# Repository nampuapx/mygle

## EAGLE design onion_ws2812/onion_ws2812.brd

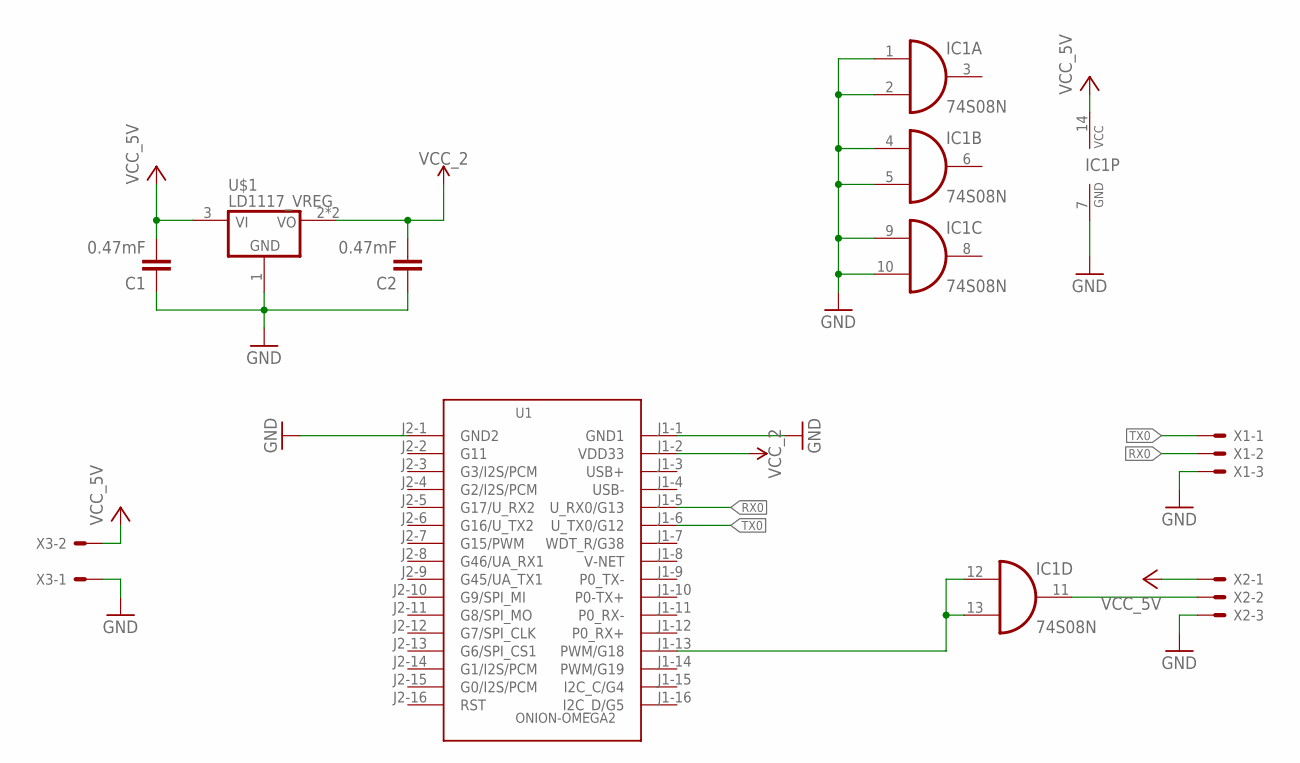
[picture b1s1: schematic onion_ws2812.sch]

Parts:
C1, C2: 0.47mF; C1206
IC1: 74S08N; DIL14
U1: ONION-OMEGA2; ONION-2MM-2X16
U$1: LD1117_VREG; SOT-223
X1, X2: KK-156-3
X3: KK-156-2

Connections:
GND: C1.1, C2.1, IC1.1 (I0), IC1.2 (I1), IC1.4 (I0), IC1.5 (I1), IC1.7 (GND), IC1.9 (I0), IC1.10 (I1), U1.J1-1 (GND1), U1.J2-1 (GND2), U$1.1 (GND), X1.3, X2.3, X3.1
unnamed: IC1.12 (I0), IC1.13 (I1), U1.J1-13 (PWM/G18)
unnamed: IC1.11 (O), X2.2
RX0: U1.J1-5 (U_RX0/G13), X1.2
TX0: U1.J1-6 (U_TX0/G12), X1.1
VCC: C1.2, IC1.14 (VCC), U$1.3 (VIN), X2.1, X3.2
VCC_2: C2.2, U1.J1-2 (VDD33), U$1.2 (VOUT), U$1.TAB (VOUT)

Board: 2 copper layers, 8 parts (0 on the bottom side), 7 nets, no tracks yet.

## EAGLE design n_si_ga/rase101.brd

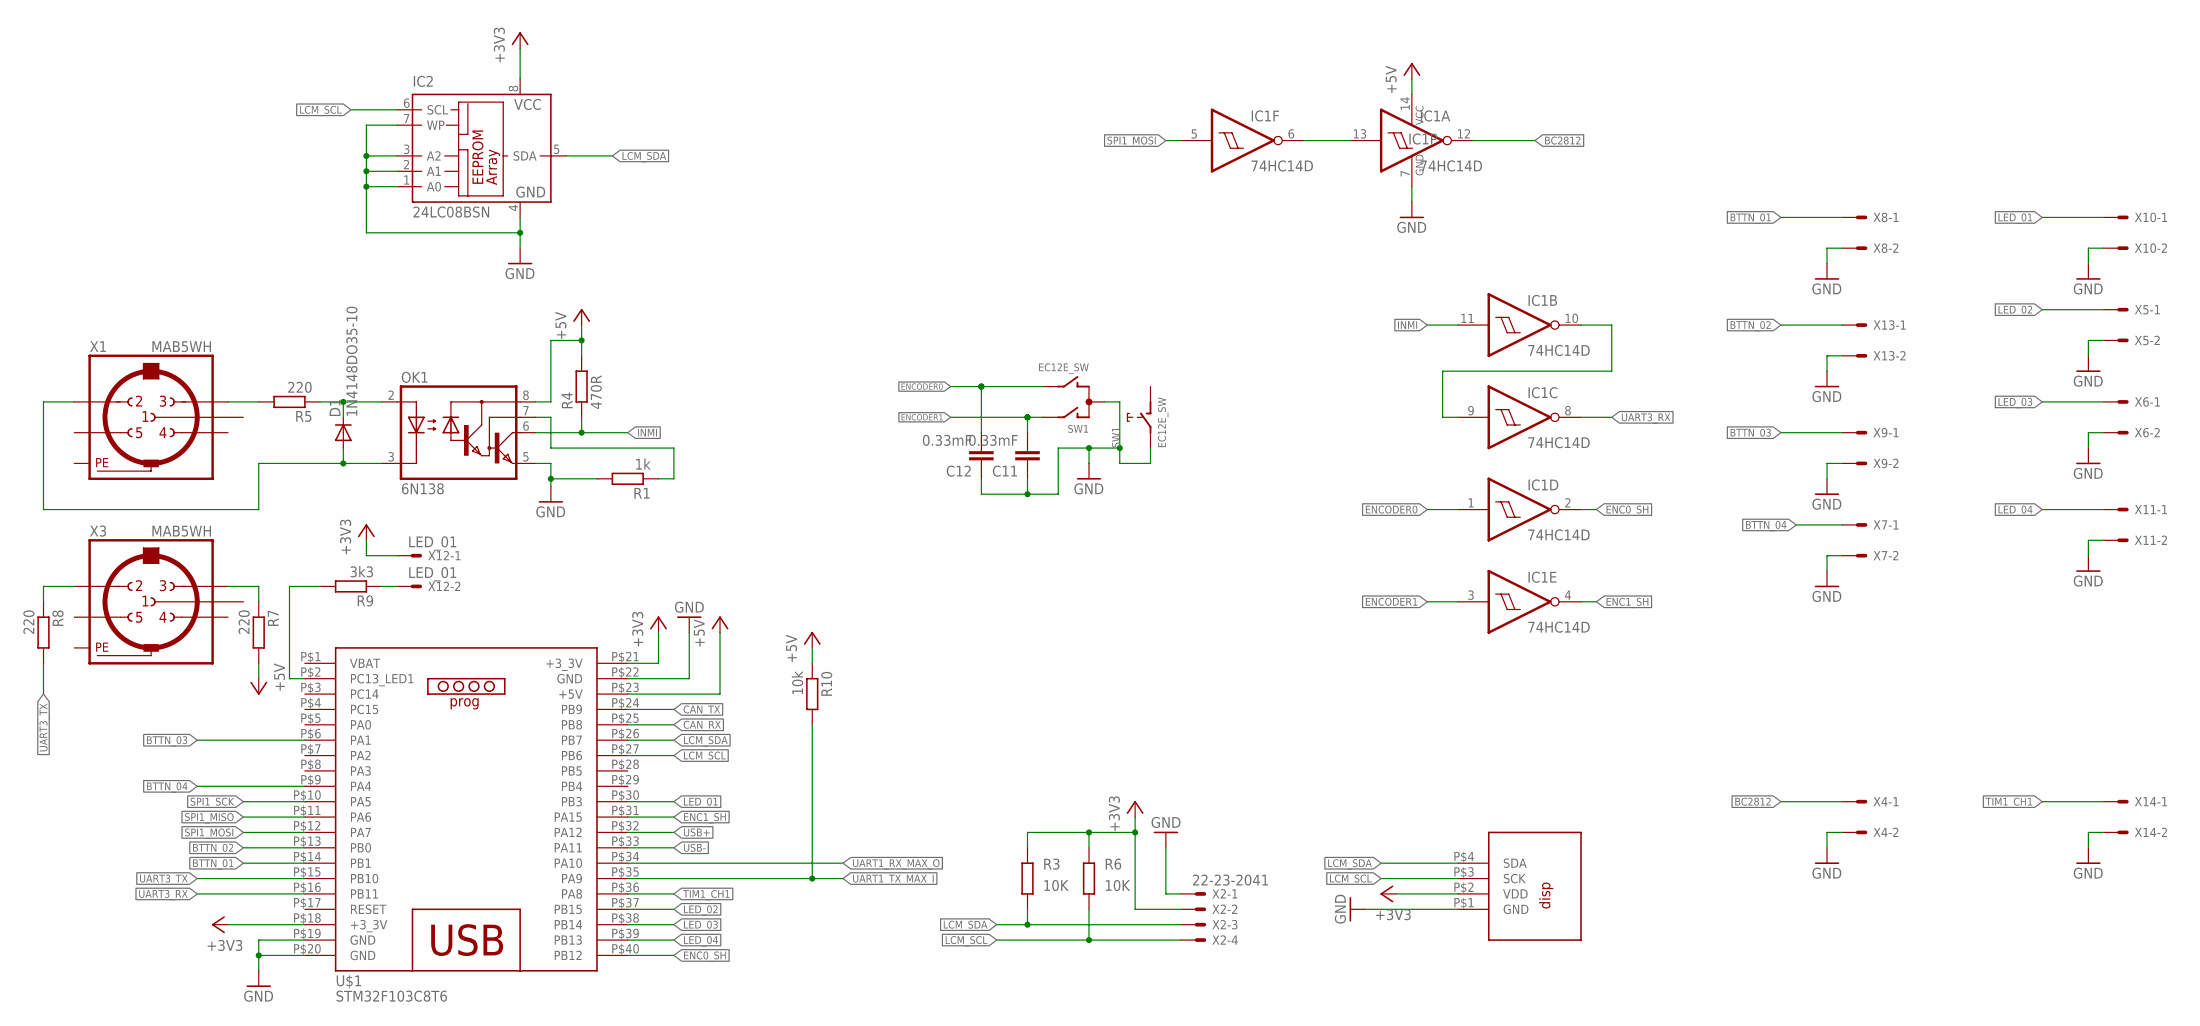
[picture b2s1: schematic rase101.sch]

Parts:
C11, C12: 0.33mF; C1206
D1: 1N4148DO35-10; DO35-10
IC1: 74HC14D; SO14
IC2: 24LC08BSN; SO-08
OK1: 6N138; DIL08
R1: 1k; M1206
R3, R6: 10K; R1206
R4: 470R; M1206
R5, R7, R8: 220; M1206
R9: 3k3; M1206
R10: 10k; M1206
SW1: EC12E_SW; ALPS_EC12E_SW
U$1: STM32F103C8T6
U$3: OLED_0.96
X1, X3: MAB5WH
X2: 22-23-2041
X4, X5, X6, X7, X8, X9, X10, X11, X13, X14: KK-156-2
X12: LED_01; KK-156-2

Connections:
+3V3: IC2.8 (VCC), R3.1, R6.1, U$1.P$18 (+3_3V), U$1.P$21 (+3_3V), U$3.P$2 (VDD), X2.2, X12.1
+5V: IC1.14 (VCC), OK1.8 (VCC), R4.2, R7.2, R10.1, U$1.P$23 (+5V)
BC2812: IC1.12 (O), X4.1
BTTN_01: U$1.P$14 (PB1), X8.1
BTTN_02: U$1.P$13 (PB0), X13.1
BTTN_03: X9.1
BTTN_04: X7.1
CAN_RX: U$1.P$25 (PB8)
CAN_TX: U$1.P$24 (PB9)
ENC0_SH: IC1.2 (O)
ENC1_SH: IC1.4 (O), U$1.P$31 (PA15)
ENCODER0: C12.2, IC1.1 (I), SW1.B
ENCODER1: C11.2, IC1.3 (I), SW1.A
GND: C11.1, C12.1, IC1.7 (GND), IC2.1 (A0), IC2.2 (A1), IC2.3 (A2), IC2.4 (GND), IC2.7 (WP), OK1.5 (GND), R1.2, SW1.C, SW1.E (2), U$1.P$19 (GND), U$1.P$20 (GND), U$1.P$22 (GND), U$3.P$1 (GND), X2.1, X4.2, X5.2, X6.2, X7.2, X8.2, X9.2, X10.2, X11.2, X13.2, X14.2
INMI: IC1.11 (I), OK1.6 (VO), R4.1
LCM_SCL: R6.2, U$1.P$27 (PB6), U$3.P$3 (SCK), X2.4
LCM_SDA: R3.2, U$1.P$26 (PB7), U$3.P$4 (SDA), X2.3
LED_01: U$1.P$30 (PB3), X10.1
LED_02: U$1.P$37 (PB15), X5.1
LED_03: U$1.P$38 (PB14), X6.1
LED_04: U$1.P$39 (PB13), X11.1
unnamed: R8.1, X3.2
unnamed: R7.1, X3.3
unnamed: IC1.9 (I), IC1.10 (O)
unnamed: D1.C, OK1.2 (A), R5.1
unnamed: R5.2, X1.3
unnamed: D1.A, OK1.3 (C), X1.2
unnamed: OK1.7 (VB), R1.1
unnamed: R9.1, X12.2
unnamed: IC1.6 (O), IC1.13 (I)
unnamed: R9.2, U$1.P$2 (PC13_LED1)
PE: X1.PE, X1.PE@ (PE), X3.PE, X3.PE@ (PE)
SPI1_MISO: U$1.P$11 (PA6)
SPI1_MOSI: IC1.5 (I), U$1.P$12 (PA7)
SPI1_SCK: U$1.P$10 (PA5)
TIM1_CH1: U$1.P$36 (PA8), X14.1
UART1_RX_MAX_O: U$1.P$34 (PA10)
UART1_TX_MAX_I: R10.2, U$1.P$35 (PA9)
UART3_RX: IC1.8 (O)
UART3_TX: R8.2
USB+: U$1.P$32 (PA12)
USB-: U$1.P$33 (PA11)

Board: 2 copper layers, 32 parts (6 on the bottom side), 30 nets, no tracks yet.

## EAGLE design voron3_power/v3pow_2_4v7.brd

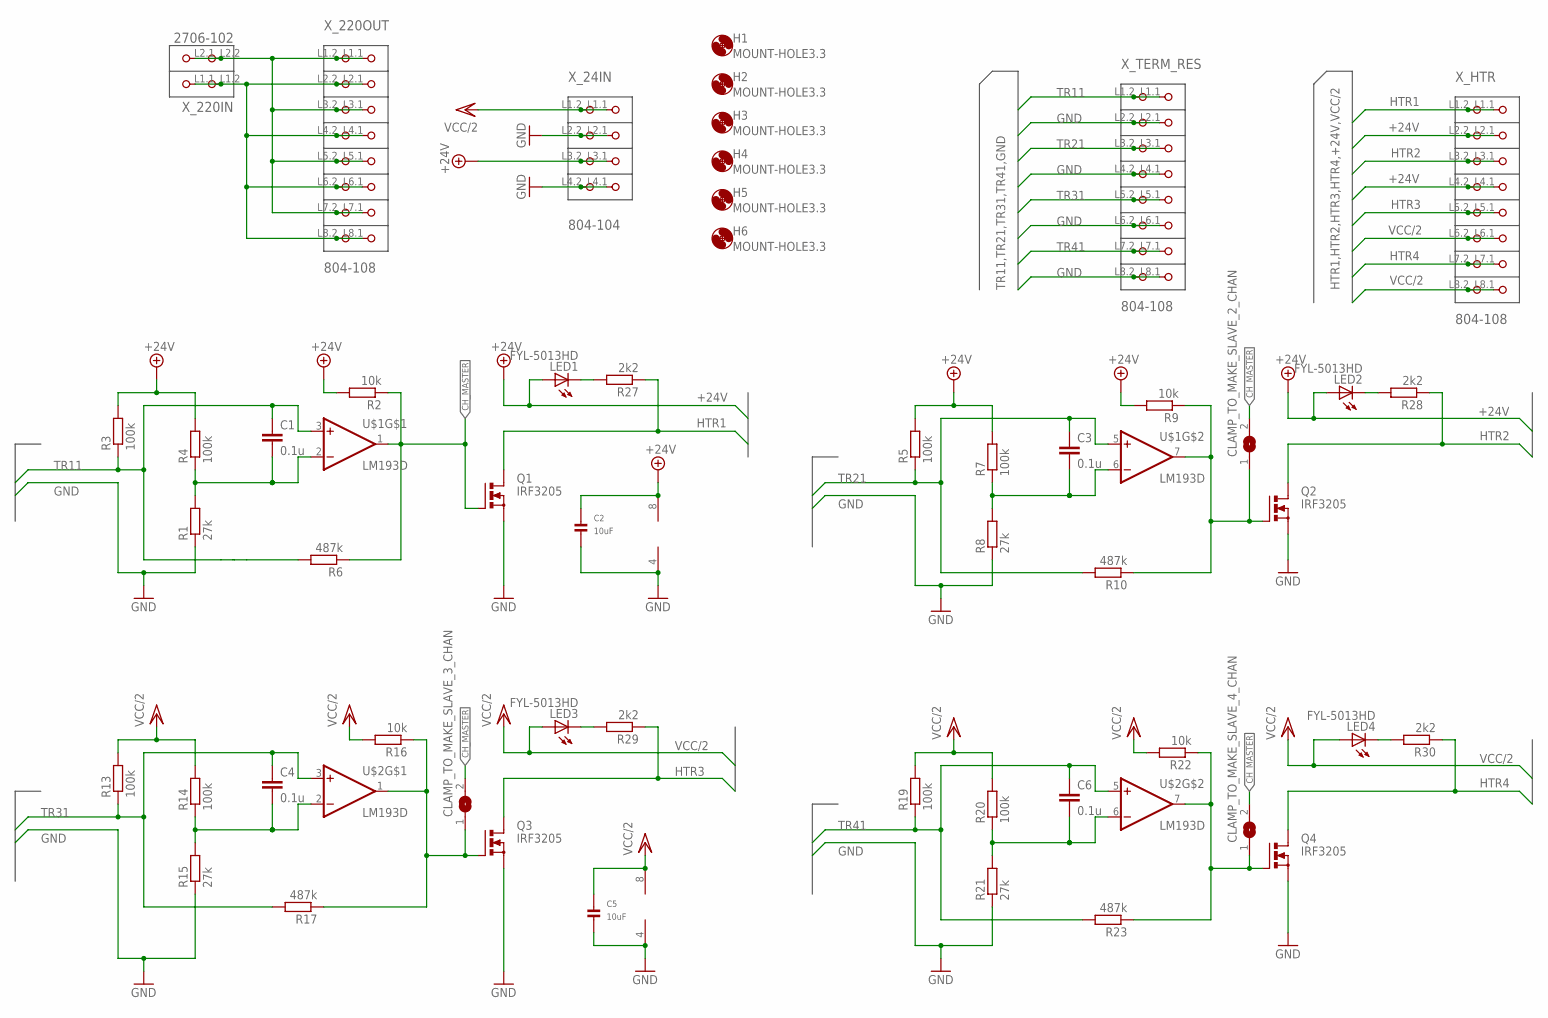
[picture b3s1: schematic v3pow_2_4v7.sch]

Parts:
C1, C3, C4, C6: 0.1u; C0805
C2, C5: 10uF; 1206
CLAMP_TO_MAKE_SLAVE_2_CHAN, CLAMP_TO_MAKE_SLAVE_3_CHAN, CLAMP_TO_MAKE_SLAVE_4_CHAN: SJ
H1, H2, H3, H4, H5, H6: MOUNT-HOLE3.3; 3,3
LED1, LED2, LED3, LED4: FYL-5013HD; LED5MM
Q1, Q2, Q3, Q4: IRF3205; TO220BV
R1, R8, R15, R21: 27k; M0805
R2, R9, R16, R22: 10k; M0805
R3, R4, R5, R7, R13, R14, R19, R20: 100k; M0805
R6, R10, R17, R23: 487k; M0805
R27, R28, R29, R30: 2k2; M0805
U$1, U$2: LM193D; SO08
X_24IN: 804-104; P-804-104
X_220IN: 2706-102; P-2706-102
X_220OUT: 804-108; P-804-108
X_HTR: 804-108; P-804-108
X_TERM_RES: 804-108; P-804-108

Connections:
+24V: C2.1, LED1.A, LED2.A, R2.2, R3.2, R4.2, R5.2, R7.2, R9.2, U$1.8 (V+), X_24IN.L3.1 (P3.1), X_24IN.L3.2 (P3.2), X_HTR.L2.1 (P2.1), X_HTR.L2.2 (P2.2), X_HTR.L4.1 (P4.1), X_HTR.L4.2 (P4.2)
CH_MASTER: CLAMP_TO_MAKE_SLAVE_2_CHAN.2, CLAMP_TO_MAKE_SLAVE_3_CHAN.2, CLAMP_TO_MAKE_SLAVE_4_CHAN.2, Q1.G, R2.1, R6.1, U$1.1 (OUT)
GND: C2.2, C5.2, Q1.S, Q2.S, Q3.S, Q4.S, R1.1, R8.1, R15.1, R21.1, U$1.4 (V-), U$2.4 (V-), X_24IN.L2.1 (P2.1), X_24IN.L2.2 (P2.2), X_24IN.L4.1 (P4.1), X_24IN.L4.2 (P4.2), X_TERM_RES.L2.1 (P2.1), X_TERM_RES.L2.2 (P2.2), X_TERM_RES.L4.1 (P4.1), X_TERM_RES.L4.2 (P4.2), X_TERM_RES.L6.1 (P6.1), X_TERM_RES.L6.2 (P6.2), X_TERM_RES.L8.1 (P8.1), X_TERM_RES.L8.2 (P8.2)
HTR1: Q1.D, R27.1, X_HTR.L1.1 (P1.1), X_HTR.L1.2 (P1.2)
HTR2: Q2.D, R28.1, X_HTR.L3.1 (P3.1), X_HTR.L3.2 (P3.2)
HTR3: Q3.D, R29.1, X_HTR.L5.1 (P5.1), X_HTR.L5.2 (P5.2)
HTR4: Q4.D, R30.1, X_HTR.L7.1 (P7.1), X_HTR.L7.2 (P7.2)
N44: X_220IN.L2.1 (P2.1), X_220IN.L2.2 (P2.2), X_220OUT.L1.1 (P1.1), X_220OUT.L1.2 (P1.2), X_220OUT.L3.1 (P3.1), X_220OUT.L3.2 (P3.2), X_220OUT.L5.1 (P5.1), X_220OUT.L5.2 (P5.2), X_220OUT.L7.1 (P7.1), X_220OUT.L7.2 (P7.2)
unnamed: CLAMP_TO_MAKE_SLAVE_3_CHAN.1, Q3.G, R16.1, R17.1, U$2.1 (OUT)
unnamed: CLAMP_TO_MAKE_SLAVE_2_CHAN.1, Q2.G, R9.1, R10.1, U$1.7 (OUT)
unnamed: CLAMP_TO_MAKE_SLAVE_4_CHAN.1, Q4.G, R22.1, R23.1, U$2.7 (OUT)
unnamed: C3.2, R7.1, R8.2, U$1.6 (-IN)
unnamed: C1.2, R1.2, R4.1, U$1.2 (-IN)
unnamed: C4.2, R14.1, R15.2, U$2.2 (-IN)
unnamed: C6.2, R20.1, R21.2, U$2.6 (-IN)
unnamed: LED1.K (C), R27.2
unnamed: LED2.K (C), R28.2
unnamed: LED3.K (C), R29.2
unnamed: LED4.K (C), R30.2
NN55: X_220IN.L1.1 (P1.1), X_220IN.L1.2 (P1.2), X_220OUT.L2.1 (P2.1), X_220OUT.L2.2 (P2.2), X_220OUT.L4.1 (P4.1), X_220OUT.L4.2 (P4.2), X_220OUT.L6.1 (P6.1), X_220OUT.L6.2 (P6.2), X_220OUT.L8.1 (P8.1), X_220OUT.L8.2 (P8.2)
TR11: C1.1, R3.1, R6.2, U$1.3 (+IN), X_TERM_RES.L1.1 (P1.1), X_TERM_RES.L1.2 (P1.2)
TR21: C3.1, R5.1, R10.2, U$1.5 (+IN), X_TERM_RES.L3.1 (P3.1), X_TERM_RES.L3.2 (P3.2)
TR31: C4.1, R13.1, R17.2, U$2.3 (+IN), X_TERM_RES.L5.1 (P5.1), X_TERM_RES.L5.2 (P5.2)
TR41: C6.1, R19.1, R23.2, U$2.5 (+IN), X_TERM_RES.L7.1 (P7.1), X_TERM_RES.L7.2 (P7.2)
VCC/2: C5.1, LED3.A, LED4.A, R13.2, R14.2, R16.2, R19.2, R20.2, R22.2, U$2.8 (V+), X_24IN.L1.1 (P1.1), X_24IN.L1.2 (P1.2), X_HTR.L6.1 (P6.1), X_HTR.L6.2 (P6.2), X_HTR.L8.1 (P8.1), X_HTR.L8.2 (P8.2)

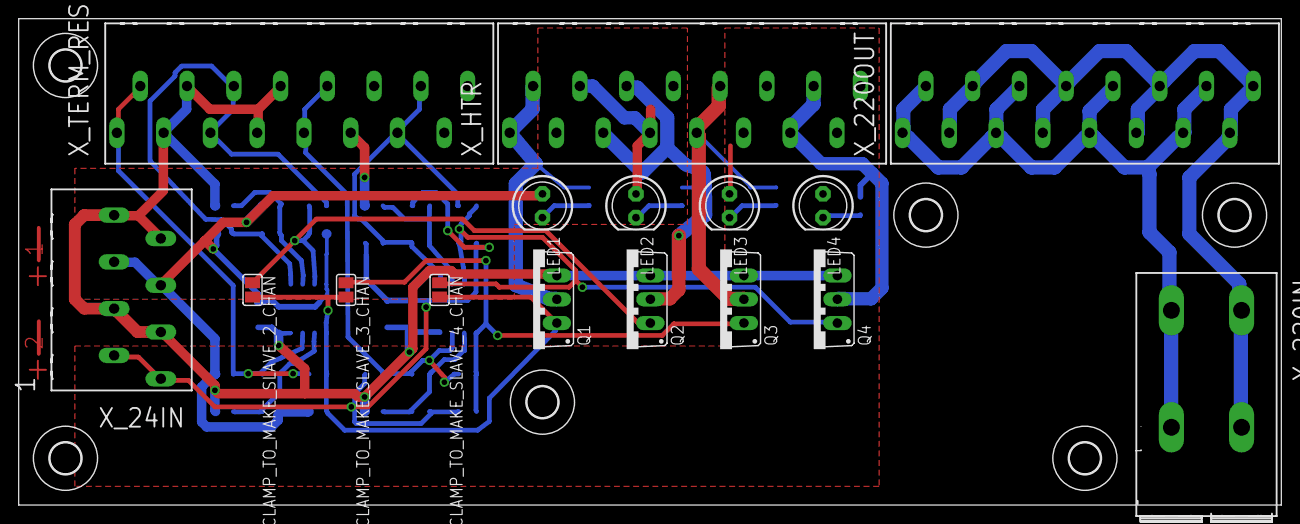
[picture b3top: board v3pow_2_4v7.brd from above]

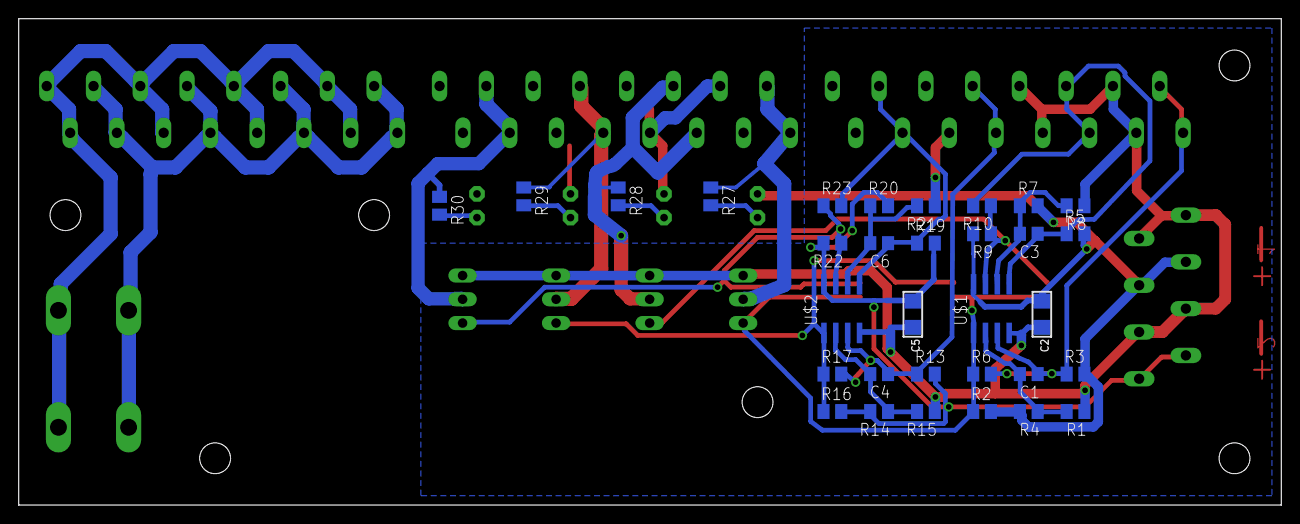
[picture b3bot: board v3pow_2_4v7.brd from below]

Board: 2 copper layers, 135.0 x 52.0 mm, 54 parts (32 on the bottom side), 25 nets.

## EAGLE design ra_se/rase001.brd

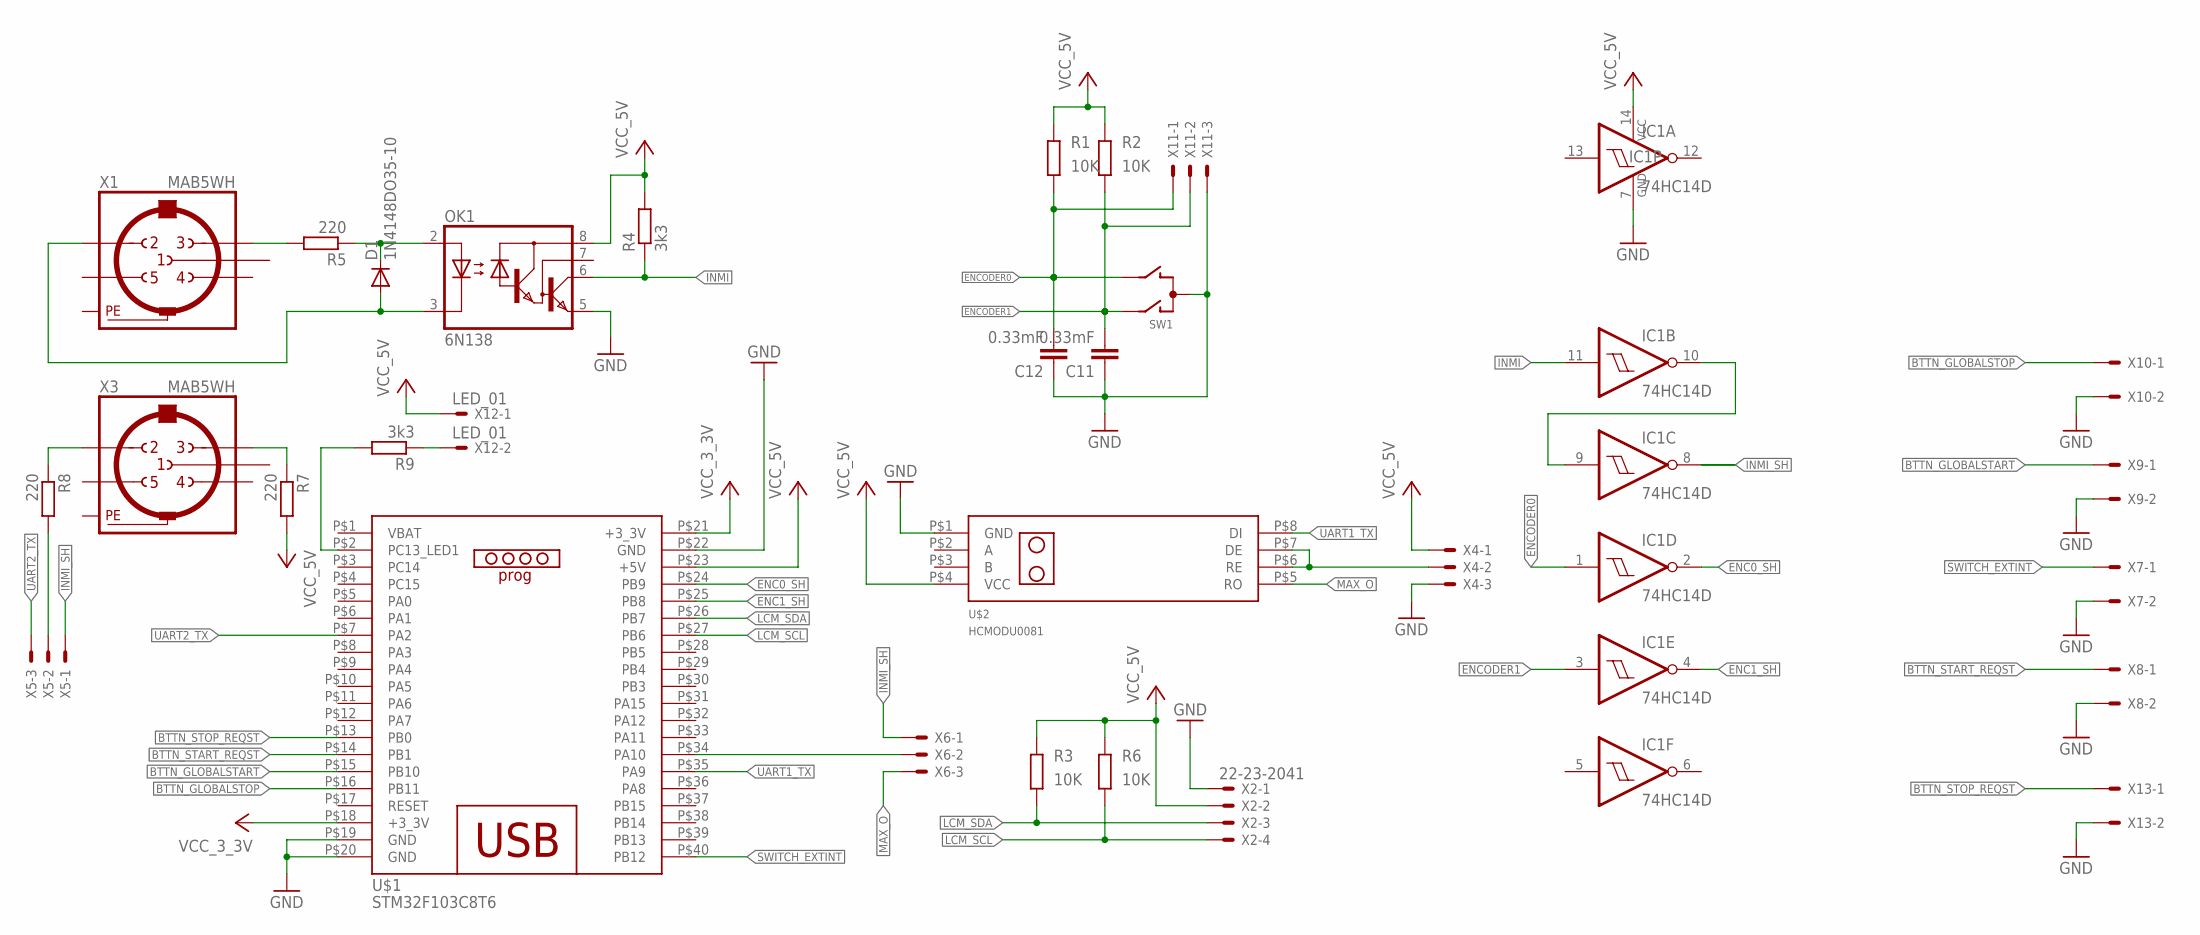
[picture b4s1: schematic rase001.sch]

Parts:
C11, C12: 0.33mF; C1206
D1: 1N4148DO35-10; DO35-10
IC1: 74HC14D; SO14
OK1: 6N138; DIL08
R1, R2, R3, R6: 10K; R1206
R4, R9: 3k3; M1206
R5, R7, R8: 220; M1206
SW1: EC12E_SW; ALPS_EC12E_SW
U$1: STM32F103C8T6
U$2: HCMODU0081
X1, X3: MAB5WH
X2: 22-23-2041
X4, X5, X6, X11: KK-156-3
X7, X8, X9, X10, X13: KK-156-2
X12: LED_01; KK-156-2

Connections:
BTTN_GLOBALSTART: U$1.P$15 (PB10), X9.1
BTTN_GLOBALSTOP: U$1.P$16 (PB11), X10.1
BTTN_START_REQST: U$1.P$14 (PB1), X8.1
BTTN_STOP_REQST: U$1.P$13 (PB0), X13.1
ENC0_SH: IC1.2 (O), U$1.P$24 (PB9)
ENC1_SH: IC1.4 (O), U$1.P$25 (PB8)
ENCODER0: C12.2, R1.2, SW1.B, X11.1
ENCODER1: C11.2, R2.2, SW1.A, X11.2
GND: C11.1, C12.1, IC1.7 (GND), OK1.5 (GND), SW1.C, U$1.P$19 (GND), U$1.P$20 (GND), U$1.P$22 (GND), U$2.P$1 (GND), X2.1, X4.3, X7.2, X8.2, X9.2, X10.2, X11.3, X13.2
INMI: OK1.6 (VO), R4.1
INMI_SH: IC1.8 (O), X5.1, X6.1
LCM_SCL: R6.2, U$1.P$27 (PB6), X2.4
LCM_SDA: R3.2, U$1.P$26 (PB7), X2.3
MAX_O: U$2.P$5 (RO), X6.3
unnamed: R8.1, X3.2
unnamed: R7.1, X3.3
unnamed: IC1.9 (I), IC1.10 (O)
unnamed: D1.C, OK1.2 (A), R5.1
unnamed: R5.2, X1.3
unnamed: D1.A, OK1.3 (C), X1.2
unnamed: R8.2, X5.2
unnamed: R9.1, X12.2
unnamed: U$1.P$34 (PA10), X6.2
unnamed: U$2.P$6 (RE), U$2.P$7 (DE), X4.2
unnamed: R9.2, U$1.P$2 (PC13_LED1)
PE: X1.PE, X1.PE@ (PE), X3.PE, X3.PE@ (PE)
SWITCH_EXTINT: U$1.P$40 (PB12), X7.1
UART1_TX: U$1.P$35 (PA9), U$2.P$8 (DI)
UART2_TX: U$1.P$7 (PA2), X5.3
VCC: IC1.14 (VCC)
VCC_3V: U$1.P$18 (+3_3V), U$1.P$21 (+3_3V)
VCC_5V: OK1.8 (VCC), R1.1, R2.1, R3.1, R4.2, R6.1, R7.2, U$1.P$23 (+5V), U$2.P$4 (VCC), X2.2, X4.1, X12.1

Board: 2 copper layers, 30 parts (0 on the bottom side), 31 nets, no tracks yet.

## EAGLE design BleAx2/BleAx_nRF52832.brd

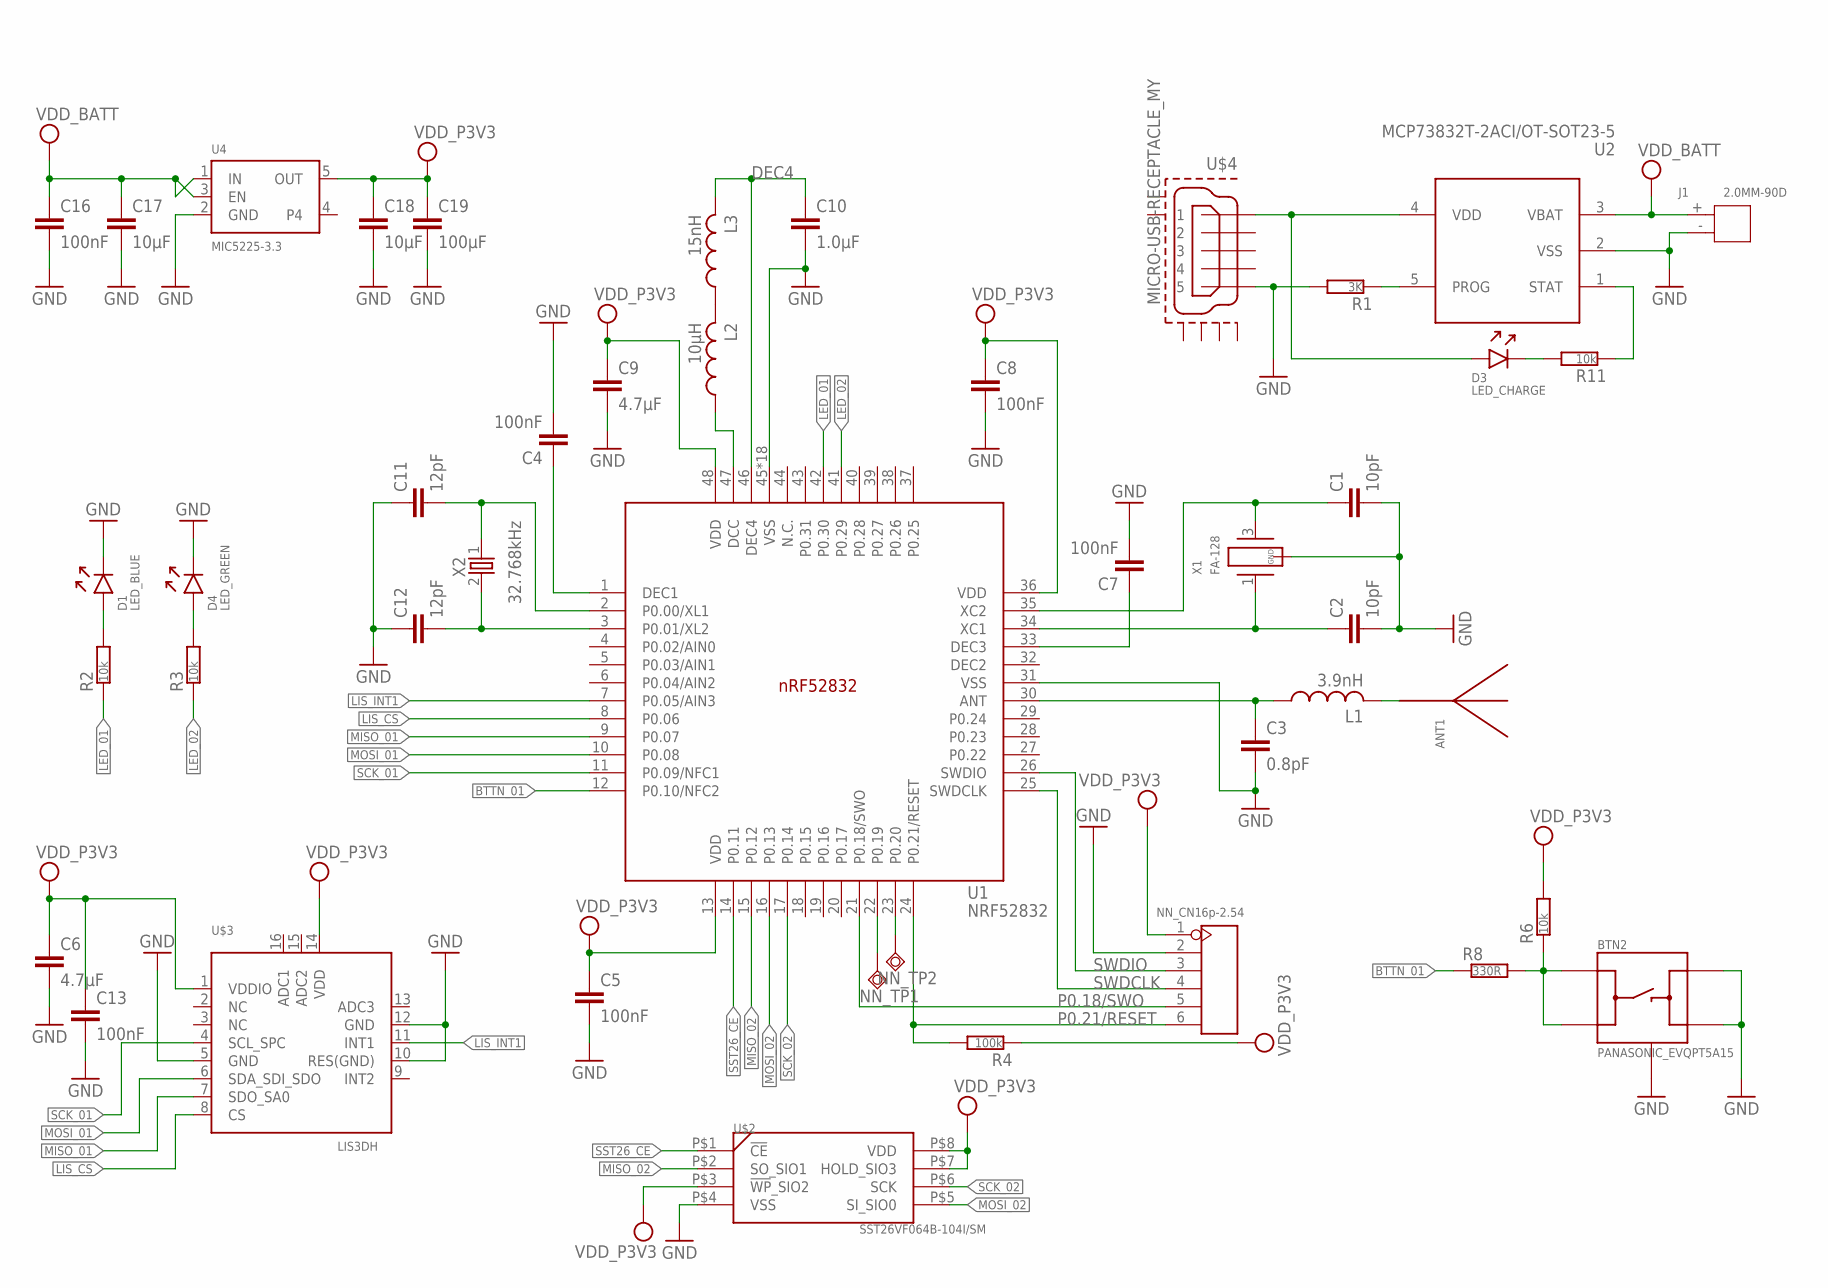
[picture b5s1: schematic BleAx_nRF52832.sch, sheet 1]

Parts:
ANT1: ANTENNA_QUARTER-WAVE_MONOPOLE_MEANDERED_LEFT; QWMP_MEANDERED_LEFT_+6
BTN2: PANASONIC_EVQPT5A15
C1, C2: 10pF; RESC0402_N
C3: 0.8pF; RESC0402_N
C4, C5, C7, C8, C13, C16: 100nF; RESC0402_N
C6, C9: 4.7µF; RESC0603_N
C10: 1.0µF; RESC0603_N
C11, C12: 12pF; RESC0402_N
C17, C18: 10µF; RESC0603_N
C19: 100µF; RESC0805_N
D1: LED_BLUE; DIOC0603_N
D3: LED_CHARGE; DIOC0603_N
D4: LED_GREEN; DIOC0603_N
J1: 2.0MM-90D; H2-2.0-90D
L1: 3.9nH; RESC0402_N
L2: 10µH; RESC0603_N
L3: 15nH; RESC0402_N
NN_CN1: 6p-2.54; H6-2.54
NN_TP1, NN_TP2: TPSQTP08R; TP08R
R1: 3K; RESC0402_N
R2, R3, R6, R11: 10k; RESC0402_N
R4: 100k; RESC0402_N
R8: 330R; RESC0402_N
U1: NRF52832; QFN40P600X600X90-48_N
U2: MCP73832T-2ACI/OT-SOT23-5; SOT-23-5
U4: MIC5225-3.3; SOT23-5
U$2: SST26VF064B-104I/SM; SOIJ8
U$3: LIS3DH; LGA16_3X3MM
U$4: MICRO-USB-RECEPTACLE_MY; 47589-0001_MY
X1: FA-128
X2: 32.768kHz; XTAL_3215_N

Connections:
ANT: C3.1, L1.1, U1.30 (ANT)
BTTN_01: R8.1, U1.12 (P0.10/NFC2)
DEC3: C7.1, U1.33 (DEC3)
DEC4: C10.1, L3.2, U1.46 (DEC4)
GND: BTN2.3 (B), BTN2.4 (B'), BTN2.5 (GND), BTN2.6 (GND), C1.2, C2.2, C3.2, C4.2, C5.2, C6.2, C7.2, C8.2, C9.2, C10.2, C11.1, C12.1, C13.2, C16.2, C17.2, C18.2, C19.2, D1.1 (C), D4.1 (C), J1.-, NN_CN1.2, R1.2, U1.31 (VSS), U1.45 (VSS), U1.PAD (VSS), U1.PAD@VIA01 (VSS), U1.PAD@VIA02 (VSS), U1.PAD@VIA03 (VSS), U1.PAD@VIA04 (VSS), U1.PAD@VIA05 (VSS), U1.PAD@VIA06 (VSS), U1.PAD@VIA07 (VSS), U1.PAD@VIA08 (VSS), U1.PAD@VIA09 (VSS), U1.PAD@VIA10 (VSS), U1.PAD@VIA11 (VSS), U1.PAD@VIA12 (VSS), U1.PAD@VIA13 (VSS), U1.PAD@VIA14 (VSS), U1.PAD@VIA15 (VSS), U1.PAD@VIA16 (VSS), U2.2 (VSS), U4.2 (GND), U$2.P$4 (VSS), U$3.5 (GND), U$3.10 (RES(GND)), U$3.12 (GND), U$4.5, X1.2 (GND), X1.4 (GND)
LED_01: R2.1, U1.42 (P0.30)
LED_02: R3.1, U1.41 (P0.29)
LIS_CS: U1.8 (P0.06), U$3.8 (CS)
LIS_INT1: U1.7 (P0.05/AIN3), U$3.11 (INT1)
MISO_01: U1.9 (P0.07), U$3.7 (SDO_SA0)
MISO_02: U1.15 (P0.12), U$2.P$2 (SO_SIO1)
MOSI_01: U1.10 (P0.08), U$3.6 (SDA_SDI_SDO)
MOSI_02: U1.16 (P0.13), U$2.P$5 (SI_SIO0)
unnamed: R1.1, U2.5 (PROG)
unnamed: L2.2, L3.1
unnamed: C1.1, U1.35 (XC2), X1.3 (2)
unnamed: L2.1, U1.47 (DCC)
unnamed: ANT1.P$1, L1.2
unnamed: BTN2.1 (A), BTN2.2 (A'), R6.1, R8.2
unnamed: D1.2 (A), R2.2
unnamed: D4.2 (A), R3.2
unnamed: D3.1 (C), R11.2
unnamed: R11.1, U2.1 (STAT)
unnamed: NN_TP1.TP, U1.22 (P0.19)
unnamed: NN_TP2.TP, U1.23 (P0.20)
unnamed: C4.1, U1.1 (DEC1)
P0.18/SWO: NN_CN1.5, U1.21 (P0.18/SWO)
P0.21/RESET: NN_CN1.6, R4.2, U1.24 (P0.21/RESET)
SCK_01: U1.11 (P0.09/NFC1), U$3.4 (SCL_SPC)
SCK_02: U1.17 (P0.14), U$2.P$6 (SCK)
SST26_CE: U1.14 (P0.11), U$2.P$1 (!CE)
SWDCLK: NN_CN1.4, U1.25 (SWDCLK)
SWDIO: NN_CN1.3, U1.26 (SWDIO)
VCC_P5V0_USB: D3.2 (A), U2.4 (VDD), U$4.1
VDD_BATT: C16.1, C17.1, J1.+, U2.3 (VBAT), U4.1 (IN), U4.3 (EN)
VDD_P3V3: C5.1, C6.1, C8.1, C9.1, C13.1, C18.1, C19.1, NN_CN1.1, R4.1, R6.2, U1.13 (VDD), U1.36 (VDD), U1.48 (VDD), U4.5 (OUT), U$2.P$3 (!WP!_SIO2), U$2.P$7 (HOLD_SIO3), U$2.P$8 (VDD), U$3.1 (VDDIO), U$3.14 (VDD)
X1: C2.1, U1.34 (XC1), X1.1
XL1: C11.2, U1.2 (P0.00/XL1), X2.1
XL2: C12.2, U1.3 (P0.01/XL2), X2.2

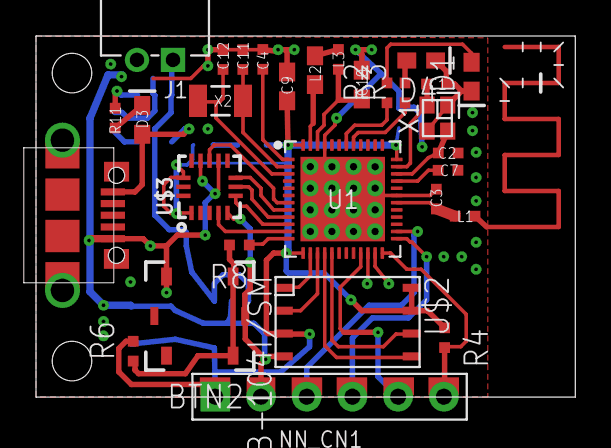
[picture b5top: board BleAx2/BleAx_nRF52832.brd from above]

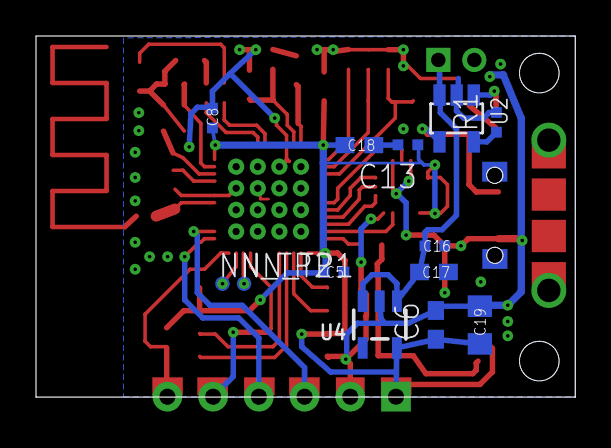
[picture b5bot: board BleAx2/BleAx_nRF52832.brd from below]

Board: 2 copper layers, 30.0 x 20.1 mm, 44 parts (13 on the bottom side), 39 nets.

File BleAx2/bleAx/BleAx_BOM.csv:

Part;Value;Device;Package;Description;MPN;TP_SIGNAL_NAME;VALUE
BTN2;PANASONIC_EVQPT5A15;PANASONIC_EVQPT5A15;PANASONIC_EVQPT5A15;;;;
C1;10pF;CAPACITOR_0402_N;RESC0402_N;Generic chip capacitor;;;
C2;10pF;CAPACITOR_0402_N;RESC0402_N;Generic chip capacitor;;;
C3;0.8pF;CAPACITOR_0402_N;RESC0402_N;Generic chip capacitor;;;
C4;100nF;CAPACITOR_0402_N;RESC0402_N;Generic chip capacitor;;;
C5;100nF;CAPACITOR_0402_N;RESC0402_N;Generic chip capacitor;;;
C6;4.7µF;CAPACITOR_0603_N;RESC0603_N;Generic chip capacitor;;;
C7;100nF;CAPACITOR_0402_N;RESC0402_N;Generic chip capacitor;;;
C8;100nF;CAPACITOR_0402_N;RESC0402_N;Generic chip capacitor;;;
C9;4.7µF;CAPACITOR_0603_N;RESC0603_N;Generic chip capacitor;;;
C10;1.0µF;CAPACITOR_0603_N;RESC0603_N;Generic chip capacitor;;;
C11;12pF;CAPACITOR_0402_N;RESC0402_N;Generic chip capacitor;;;
C12;12pF;CAPACITOR_0402_N;RESC0402_N;Generic chip capacitor;;;
C13;100nF;CAPACITOR_0402_N;RESC0402_N;Generic chip capacitor;;;
C16;100nF;CAPACITOR_0402_N;RESC0402_N;Generic chip capacitor;;;
C17;10µF;CAPACITOR_0603_N;RESC0603_N;Generic chip capacitor
C18;10µF;CAPACITOR_0603_N;RESC0603_N;Generic chip capacitor
C19;100µF;CAPACITOR_0805_N;RESC0805_N;Generic chip capacitor
D1;LED_BLUE;LED;DIOC0603_N;
D3;LED_CHARGE;LED;DIOC0603_N;
D4;LED_GREEN;LED;DIOC0603_N;
L1;3.9nH;INDUCTOR_0402_N;RESC0402_N;Generic chip inductor
L2;10µH;INDUCTOR_0603_N;RESC0603_N;Generic chip inductor
L3;15nH;INDUCTOR_0402_N;RESC0402_N;Generic chip inductor
R1;3K;RESISTOR_0402_N;RESC0402_N;Generic chip resistor
R2;10k;RESISTOR_0402_N;RESC0402_N;Generic chip resistor
R3;10k;RESISTOR_0402_N;RESC0402_N;Generic chip resistor
R4;100k;RESISTOR_0402_N;RESC0402_N;Generic chip resistor
R6;10k;RESISTOR_0402_N;RESC0402_N;Generic chip resistor
R8;330R;RESISTOR_0402_N;RESC0402_N;Generic chip resistor
R11;10k;RESISTOR_0402_N;RESC0402_N;Generic chip resistor
U$2;SST26VF064B-104I/SM;SST26VF;SOIJ8;SST26VF;;;
U$3;LIS3DH;ACCEL_LIS3DHTR;LGA16_3X3MM;LIS3DHTR 3-Axis Accelerometer with I2C/SPI Interface;;;
U$4;MICRO-USB-RECEPTACLE_MY;MICRO-USB-RECEPTACLE_MY;47589-0001_MY;MICRO USB RECEPTACLES;;;
U1;NRF52832;NRF52832;QFN40P600X600X90-48_N;nRF52832;;;
U2;MCP73832T-2ACI/OT-SOT23-5;PMIC-MCP73832T-2ACI/OT(SOT23-5);SOT-23-5;310030238;MCP73832T-2ACI/OT;;MCP73832T-2ACI/OT-SOT23-5
U4;MIC5225-3.3;VREG_SOT23-5;SOT23-5;SOT23-5 Fixed Voltage Regulators;;;
X1;FA-128;FA-128;FA-128;Epson MHz RANGE CRYSTAL UNIT;;;
X2;32.768kHz;XTAL_32KHZ;XTAL_3215_N;;;;

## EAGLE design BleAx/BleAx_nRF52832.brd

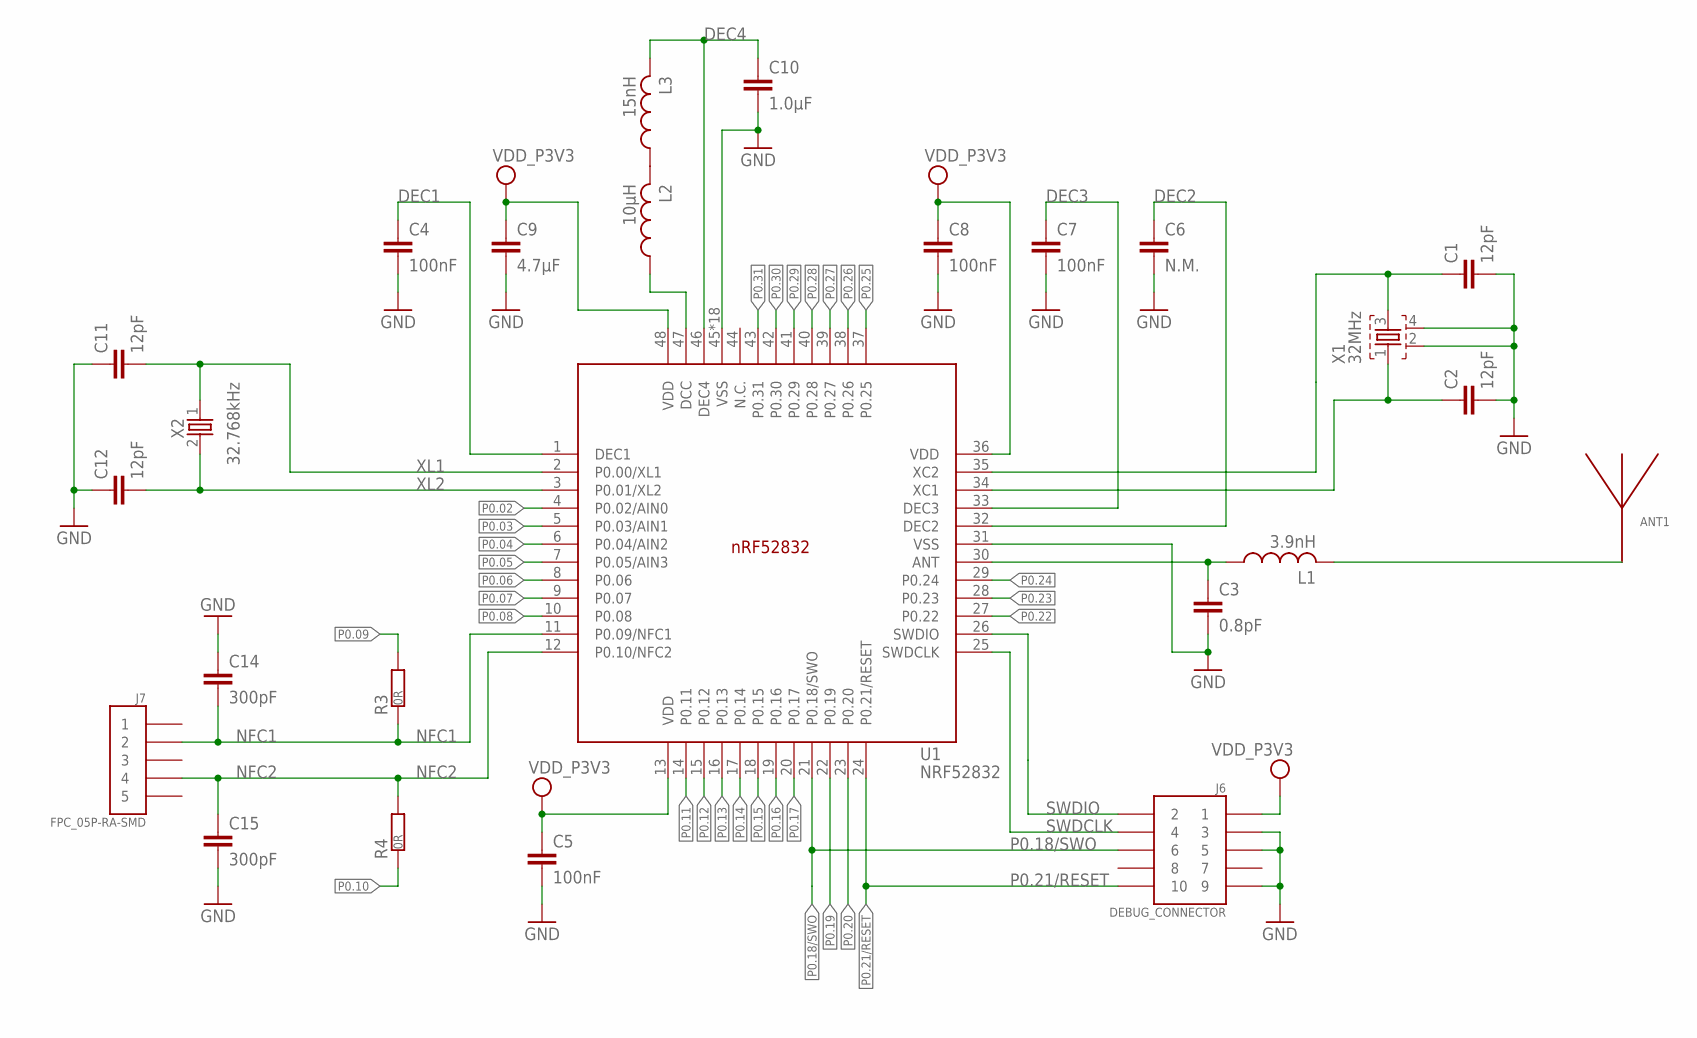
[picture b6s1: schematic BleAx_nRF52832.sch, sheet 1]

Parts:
ANT1: ANTENNA_QUARTER-WAVE_MONOPOLE_MEANDERED_LEFT; QWMP_MEANDERED_LEFT_+6
C1, C2, C11, C12: 12pF; RESC0402_N
C3: 0.8pF; RESC0402_N
C4, C5, C7, C8: 100nF; RESC0402_N
C6: N.M.; RESC0402_N
C9: 4.7µF; RESC0603_N
C10: 1.0µF; RESC0603_N
C14, C15: 300pF; RESC0402_N
J6: DEBUG_CONNECTOR; HDRV127P5X2-10_N
J7: FPC_05P-RA-SMD
L1: 3.9nH; RESC0402_N
L2: 10µH; RESC0603_N
L3: 15nH; RESC0402_N
R3, R4: 0R; RESC0402_N
U1: NRF52832; QFN40P600X600X90-48_N
X1: 32MHz; BT-XTAL_2016_N
X2: 32.768kHz; XTAL_3215_N

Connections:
ANT: C3.1, L1.1, U1.30 (ANT)
DEC1: C4.1, U1.1 (DEC1)
DEC2: C6.1, U1.32 (DEC2)
DEC3: C7.1, U1.33 (DEC3)
DEC4: C10.1, L3.2, U1.46 (DEC4)
GND: C1.2, C2.2, C3.2, C4.2, C5.2, C6.2, C7.2, C8.2, C9.2, C10.2, C11.1, C12.1, C14.1, C15.2, J6.3, J6.5, J6.9, U1.31 (VSS), U1.45 (VSS), U1.PAD (VSS), U1.PAD@VIA01 (VSS), U1.PAD@VIA02 (VSS), U1.PAD@VIA03 (VSS), U1.PAD@VIA04 (VSS), U1.PAD@VIA05 (VSS), U1.PAD@VIA06 (VSS), U1.PAD@VIA07 (VSS), U1.PAD@VIA08 (VSS), U1.PAD@VIA09 (VSS), U1.PAD@VIA10 (VSS), U1.PAD@VIA11 (VSS), U1.PAD@VIA12 (VSS), U1.PAD@VIA13 (VSS), U1.PAD@VIA14 (VSS), U1.PAD@VIA15 (VSS), U1.PAD@VIA16 (VSS), X1.2, X1.4; also elsewhere on the board
unnamed: L2.2, L3.1
unnamed: C1.1, U1.35 (XC2), X1.3
unnamed: L2.1, U1.47 (DCC)
unnamed: ANT1.P$1, L1.2
NFC1: C14.2, J7.2, R3.1, U1.11 (P0.09/NFC1)
NFC2: C15.1, J7.4, R4.2, U1.12 (P0.10/NFC2)
P0.02: U1.4 (P0.02/AIN0); also elsewhere on the board
P0.03: U1.5 (P0.03/AIN1); also elsewhere on the board
P0.04: U1.6 (P0.04/AIN2); also elsewhere on the board
P0.05: U1.7 (P0.05/AIN3); also elsewhere on the board
P0.06: U1.8 (P0.06); also elsewhere on the board
P0.07: U1.9 (P0.07); also elsewhere on the board
P0.08: U1.10 (P0.08); also elsewhere on the board
P0.09: R3.2; also elsewhere on the board
P0.10: R4.1; also elsewhere on the board
P0.11: U1.14 (P0.11); also elsewhere on the board
P0.12: U1.15 (P0.12); also elsewhere on the board
P0.13: U1.16 (P0.13); also elsewhere on the board
P0.14: U1.17 (P0.14); also elsewhere on the board
P0.15: U1.18 (P0.15); also elsewhere on the board
P0.16: U1.19 (P0.16); also elsewhere on the board
P0.17: U1.20 (P0.17); also elsewhere on the board
P0.18/SWO: J6.6, U1.21 (P0.18/SWO); also elsewhere on the board
P0.19: U1.22 (P0.19); also elsewhere on the board
P0.20: U1.23 (P0.20); also elsewhere on the board
P0.21/RESET: J6.10, U1.24 (P0.21/RESET); also elsewhere on the board
P0.22: U1.27 (P0.22); also elsewhere on the board
P0.23: U1.28 (P0.23); also elsewhere on the board
P0.24: U1.29 (P0.24); also elsewhere on the board
P0.25: U1.37 (P0.25); also elsewhere on the board
P0.26: U1.38 (P0.26); also elsewhere on the board
P0.27: U1.39 (P0.27); also elsewhere on the board
P0.28: U1.40 (P0.28); also elsewhere on the board
P0.29: U1.41 (P0.29); also elsewhere on the board
P0.30: U1.42 (P0.30); also elsewhere on the board
P0.31: U1.43 (P0.31); also elsewhere on the board
SWDCLK: J6.4, U1.25 (SWDCLK)
SWDIO: J6.2, U1.26 (SWDIO)
VDD_P3V3: C5.1, C8.1, C9.1, J6.1, U1.13 (VDD), U1.36 (VDD), U1.48 (VDD); also elsewhere on the board
X1: C2.1, U1.34 (XC1), X1.1
XL1: C11.2, U1.2 (P0.00/XL1), X2.1
XL2: C12.2, U1.3 (P0.01/XL2), X2.2

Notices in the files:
parts and their libraries:
microbuilder: This work is placed in the public domain, and may be freely used for commercial and non-commercial work with the following conditions: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
con-molex-usb_my: (C) 2014 Tomasz Boleslaw CEDRO, cederom@tlen.pl, http://www.tomek.cedro.info.
